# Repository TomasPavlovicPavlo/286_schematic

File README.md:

## Reverse engineering of 286 motherboard
This is the repository vhere I am working on reverse engineering of one 286 motherboard. It is still in progress. I use KiCad. In the PCB editor I insert fotos as background image and draw all tracks. Then I transfer all to schematic and analyse connections.

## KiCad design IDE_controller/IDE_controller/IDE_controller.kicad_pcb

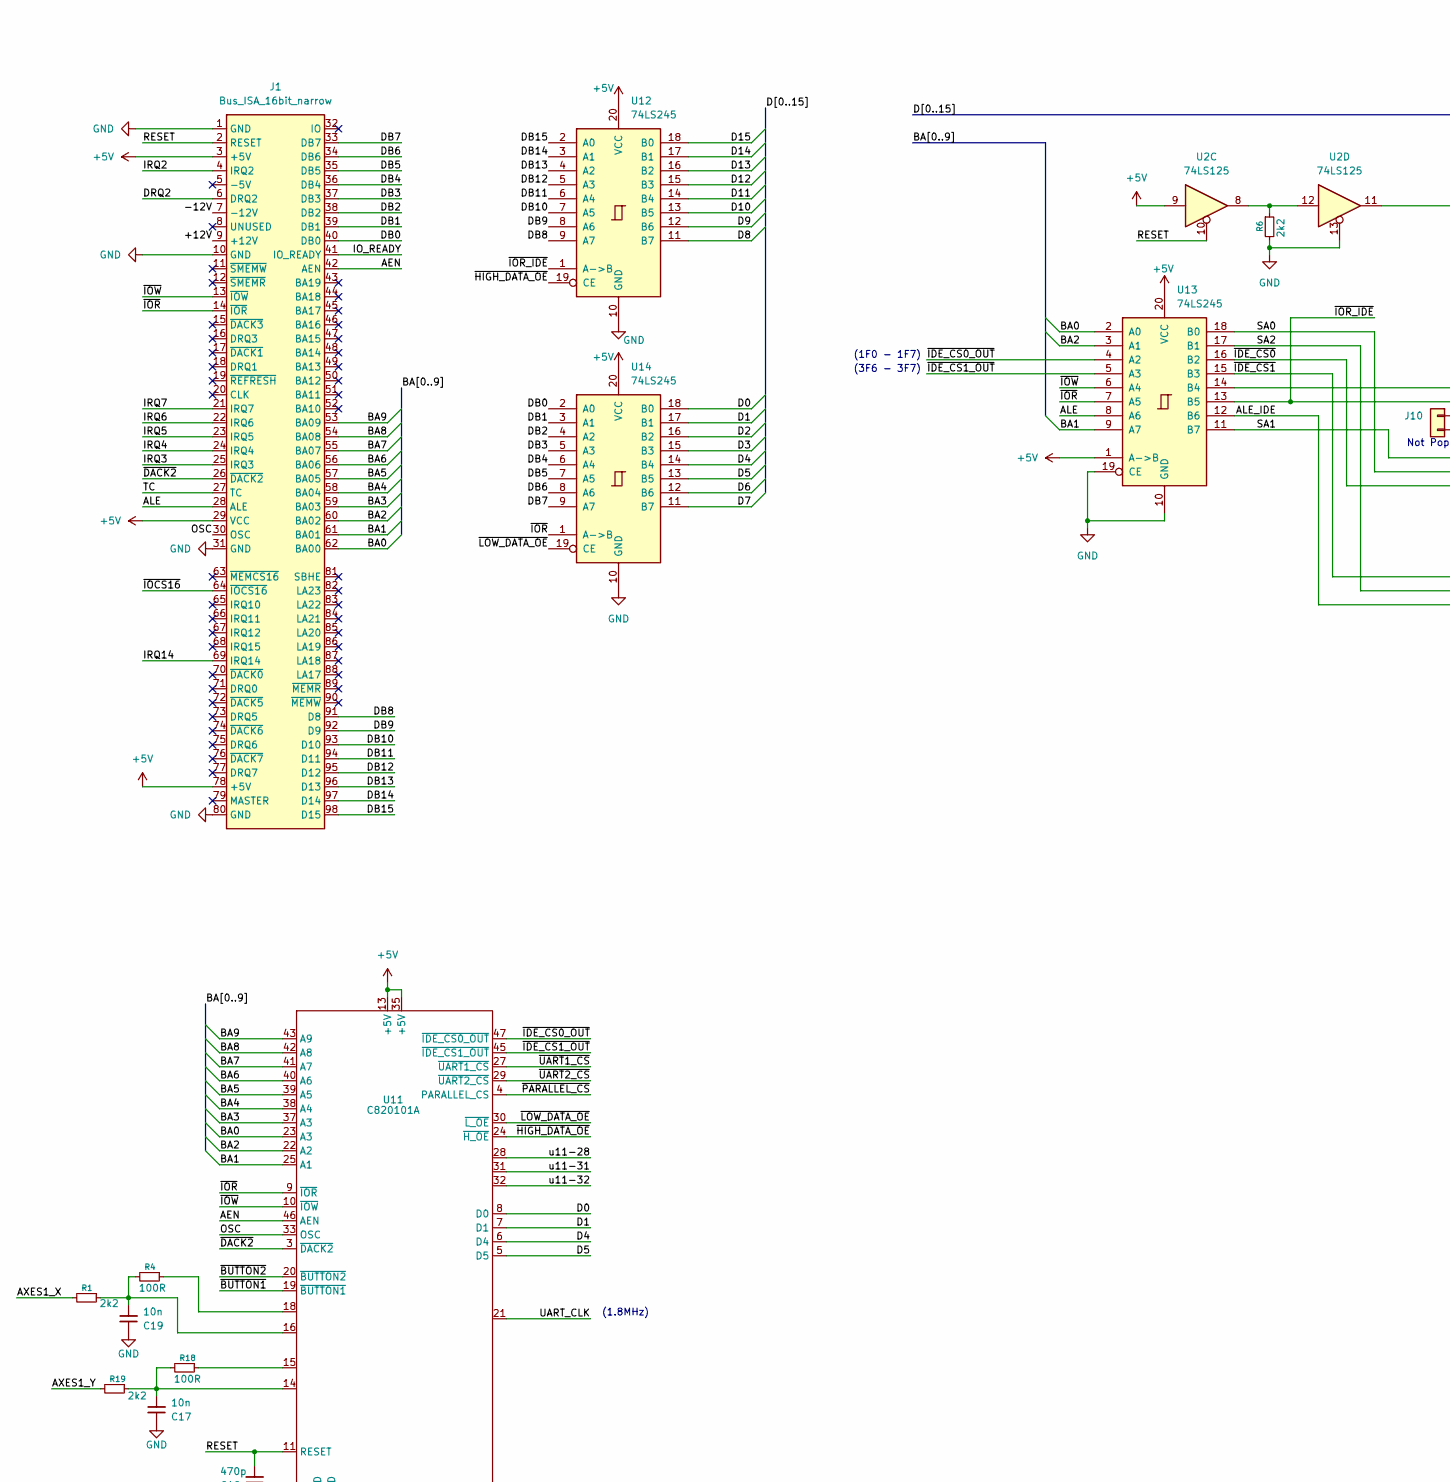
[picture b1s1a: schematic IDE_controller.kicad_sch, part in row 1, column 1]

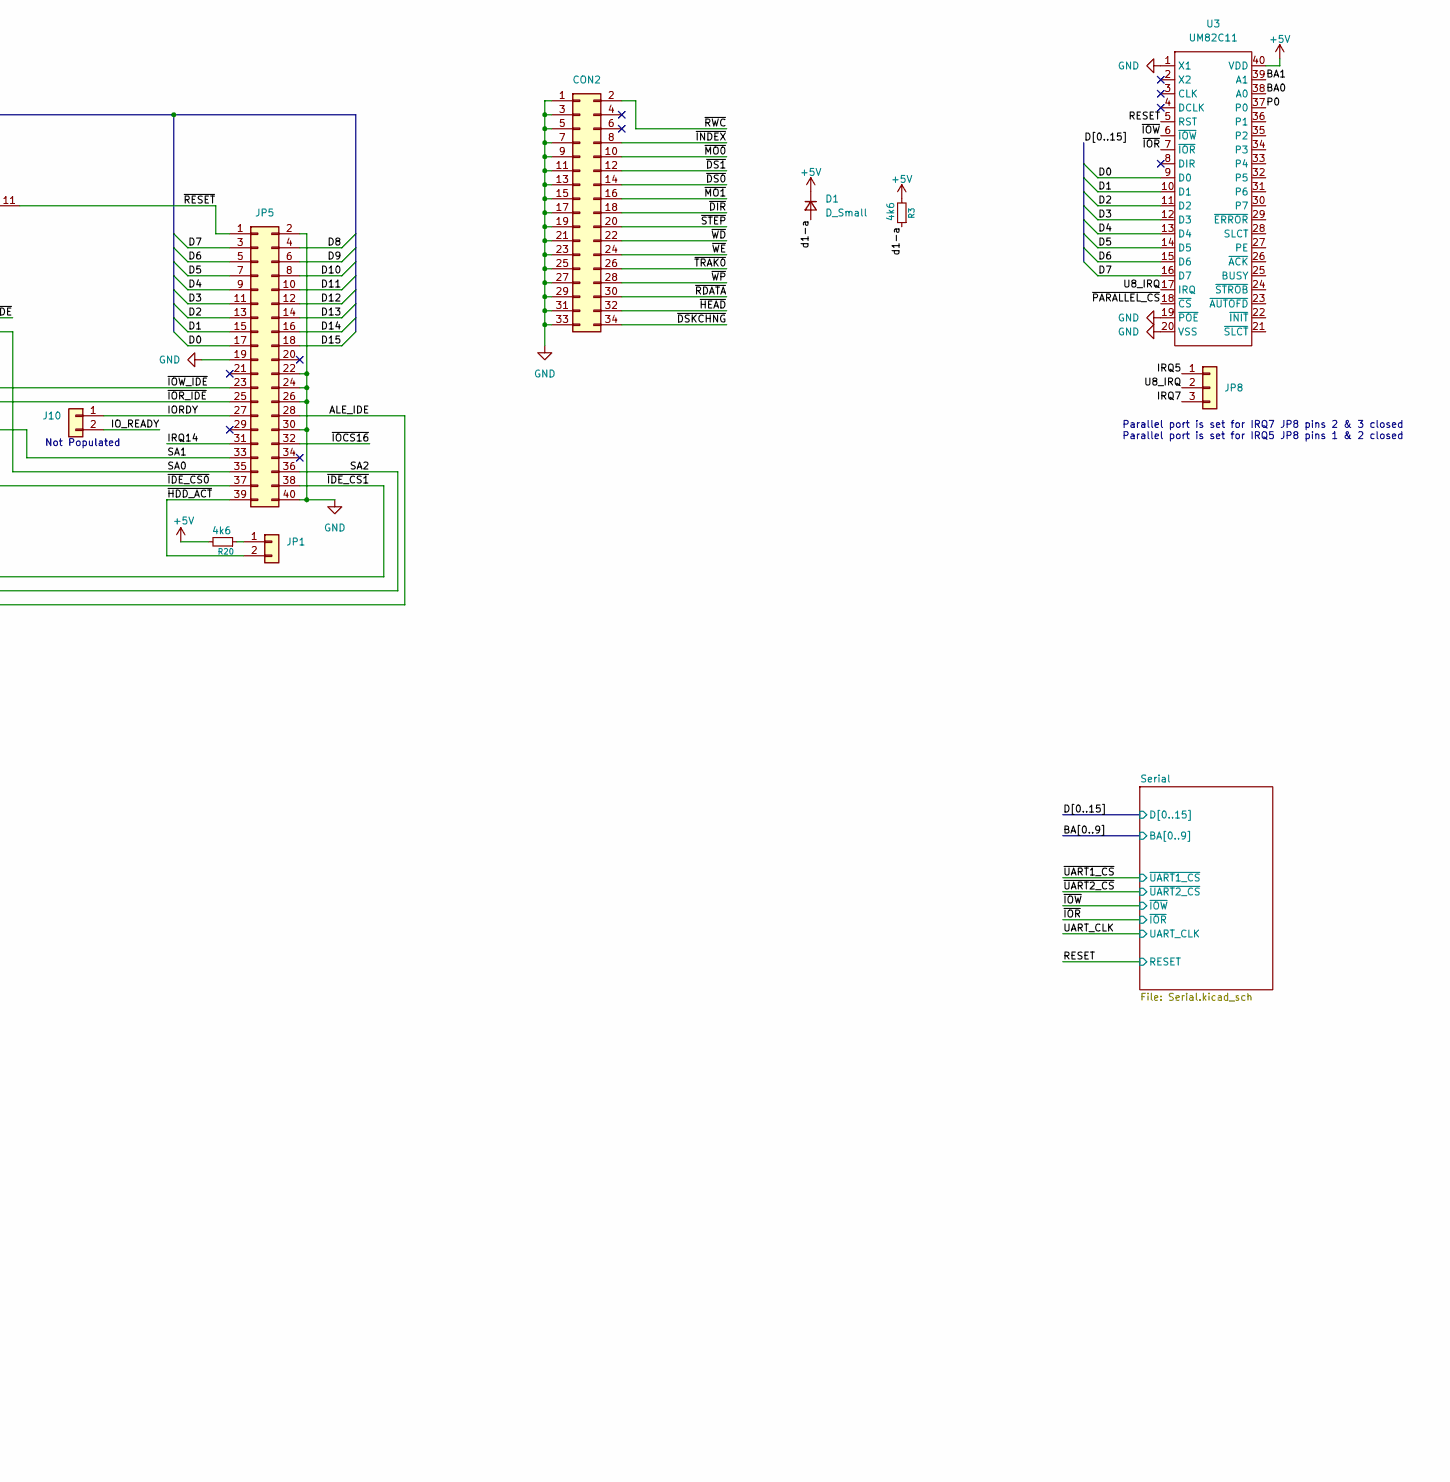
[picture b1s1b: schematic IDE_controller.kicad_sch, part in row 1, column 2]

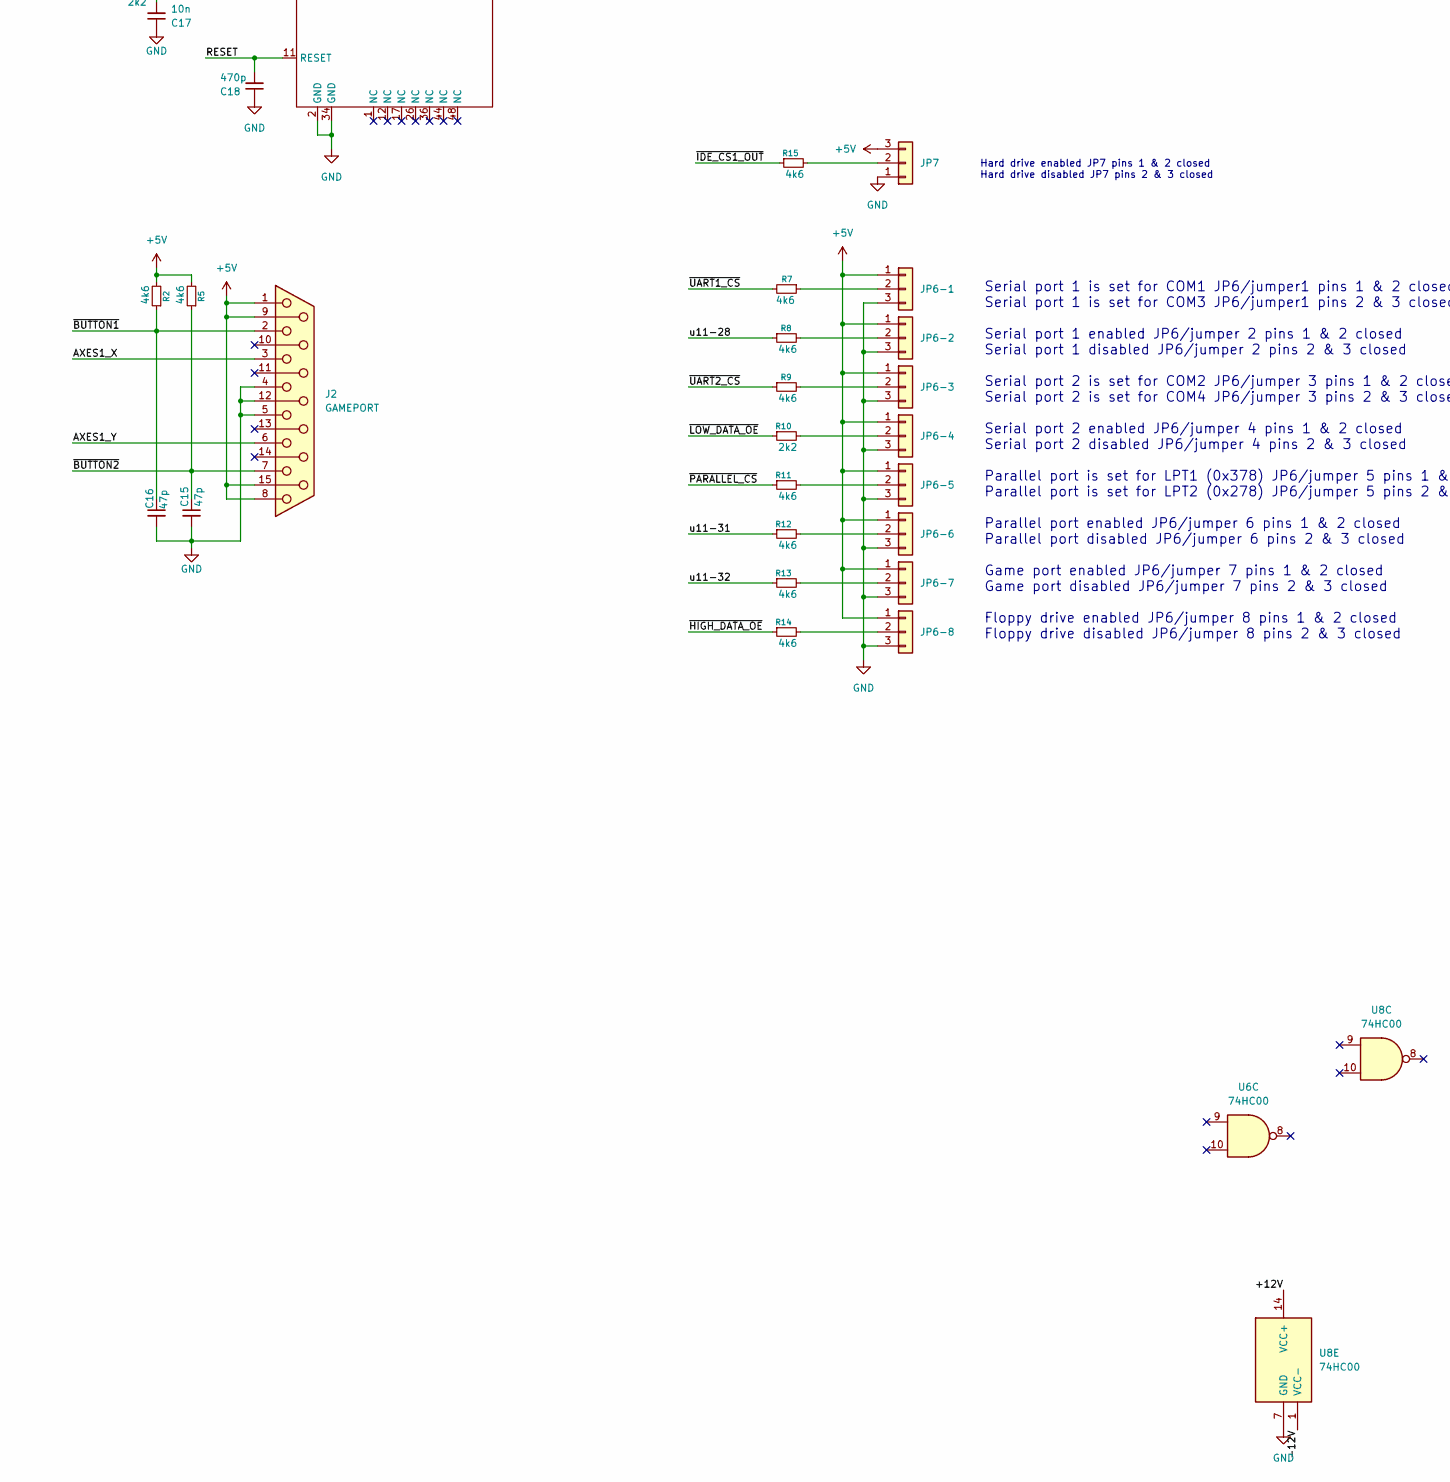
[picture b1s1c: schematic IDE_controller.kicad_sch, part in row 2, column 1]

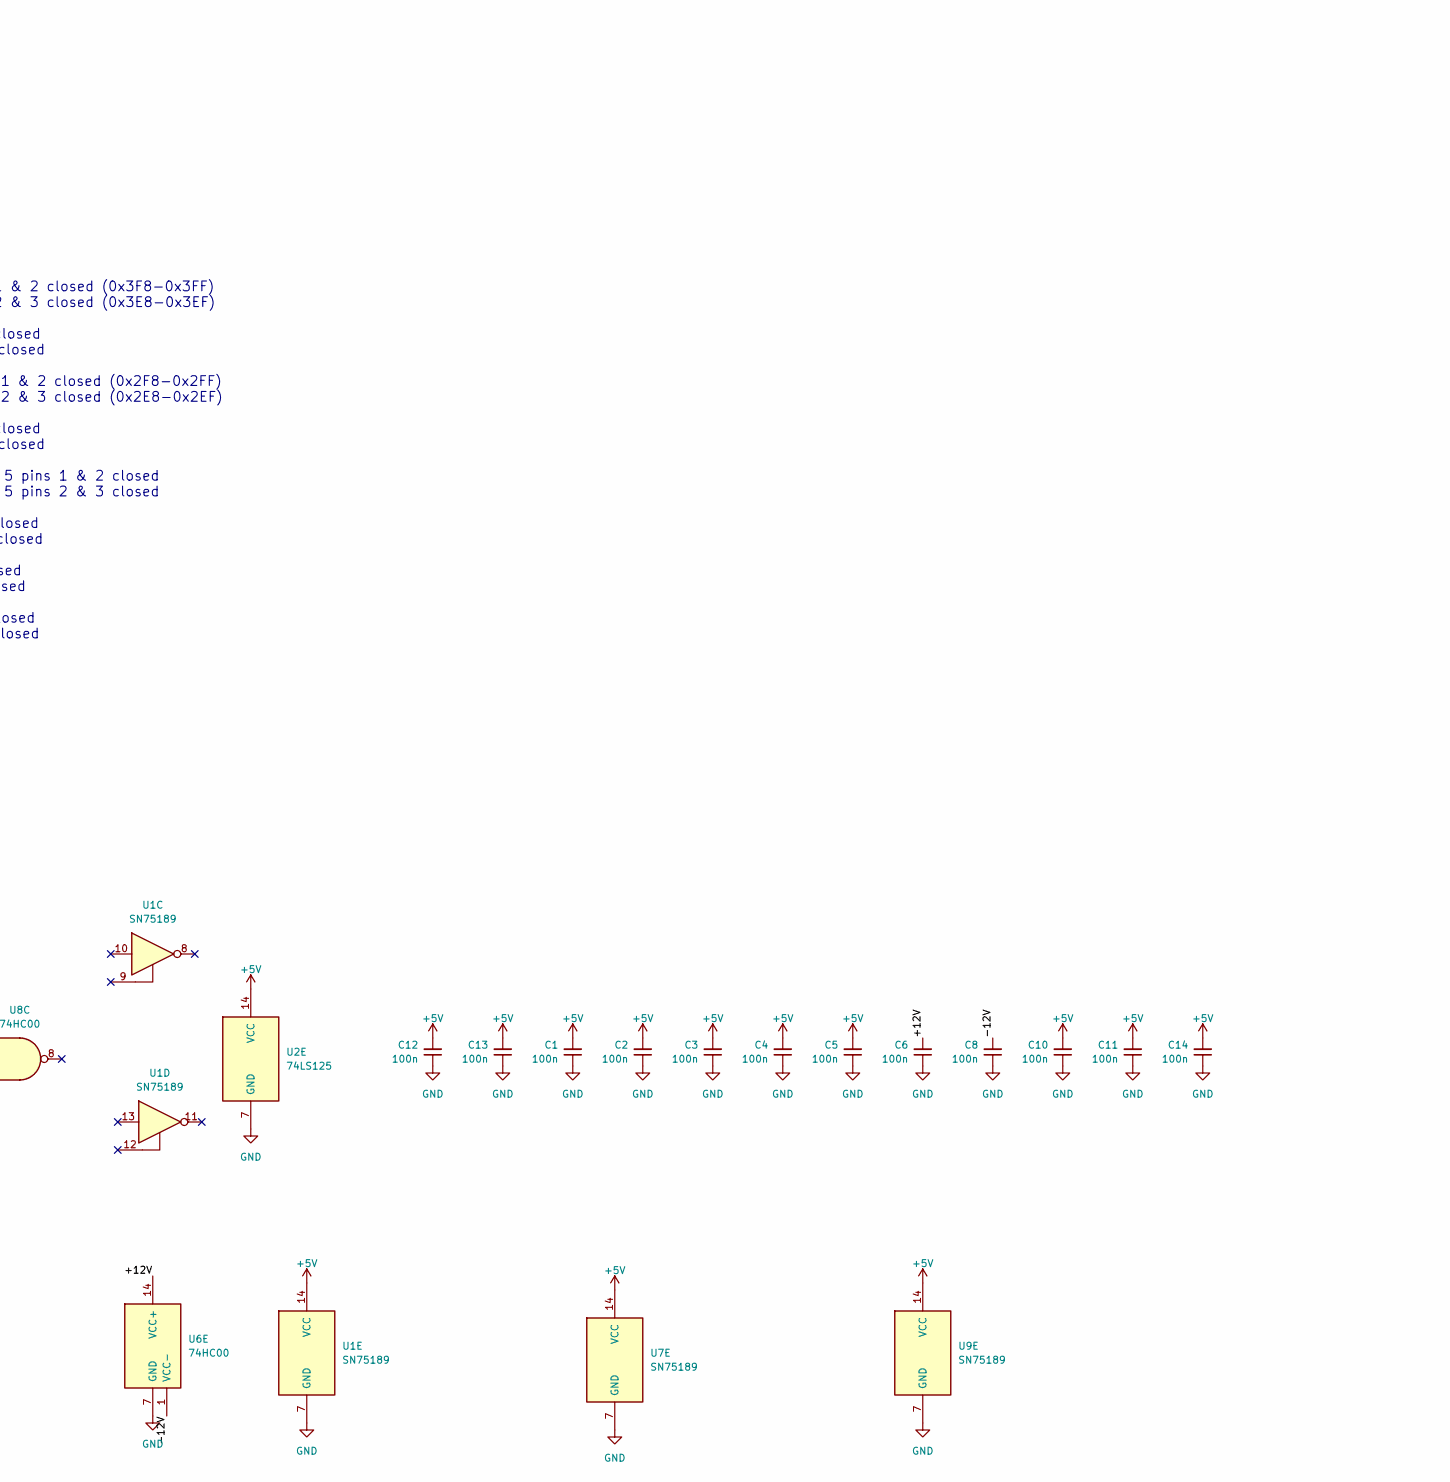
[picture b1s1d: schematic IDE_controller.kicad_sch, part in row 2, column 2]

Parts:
C1, C2, C3, C4, C5, C6, C8, C10, C11, C12, C13, C14: 100n; C_Disc_D4.3mm_W1.9mm_P5.00mm
C15, C16: 47p; C_Disc_D4.3mm_W1.9mm_P5.00mm
C17, C19: 10n; C_Disc_D4.3mm_W1.9mm_P5.00mm
C18: 470p; C_Disc_D4.3mm_W1.9mm_P5.00mm
CON2: Conn_02x17_Odd_Even; PinHeader_2x17_P2.54mm_Vertical
D1: D_Small; D_A-405_P10.16mm_Horizontal
J1: Bus_ISA_16bit_narrow; BUS_AT
J2: GAMEPORT; DSUB-15_Socket_Horizontal_P2.77x2.54mm_EdgePinOffset9.40mm
J10: Conn_01x02; PinHeader_1x02_P2.54mm_Vertical
JP1: Conn_01x02; PinHeader_1x02_P2.54mm_Vertical
JP5: Conn_02x20_Odd_Even; PinHeader_2x20_P2.54mm_Vertical
JP6-1, JP6-2, JP6-3, JP6-4, JP6-5, JP6-6, JP6-7, JP6-8, JP7, JP8: Conn_01x03; PinHeader_1x03_P2.54mm_Vertical
R1, R6, R10, R19: 2k2; R_Axial_DIN0207_L6.3mm_D2.5mm_P10.16mm_Horizontal
R2, R3, R5, R7, R8, R9, R11, R12, R13, R14, R15, R20: 4k6; R_Axial_DIN0207_L6.3mm_D2.5mm_P10.16mm_Horizontal
R4, R18: 100R; R_Axial_DIN0207_L6.3mm_D2.5mm_P10.16mm_Horizontal
U1, U7, U9: SN75189; DIP-14_W7.62mm
U2: 74LS125; DIP-14_W7.62mm
U3: UM82C11; DIP-40_W15.24mm
U6, U8: 74HC00; DIP-14_W7.62mm
U11: C820101A; LQFP-48_10x10mm_P0.7mm
U12, U13, U14: 74LS245; DIP-20_W7.62mm

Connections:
+5V: C1.2, C2.2, C3.2, C4.2, C5.2, C10.2, C11.2, C12.2, C13.2, C14.2, D1.1 (K), J1.3 (+5V), J1.29 (VCC), J1.78 (+5V), J2.1, J2.8, J2.9, J2.15, JP6-1.1, JP6-2.1, JP6-3.1, JP6-4.1, JP6-5.1, JP6-6.1, JP6-7.1, JP6-8.1, JP7.3, R2.2, R3.2, R5.2, R20.2, U1.14 (VCC), U2.9, U2.14 (VCC), U3.40 (VDD), U7.14 (VCC), U9.14 (VCC), U11.13 (+5V), U11.35 (+5V), U12.20 (VCC), U13.1 (A->B), U13.20 (VCC), U14.20 (VCC); also elsewhere on the board
/+12V: C6.2, J1.9 (+12V), U6.14 (VCC+), U8.14 (VCC+)
/-12V: C8.2, J1.7 (-12V), U6.1 (VCC-), U8.1 (VCC-)
/AEN: J1.42 (AEN), U11.46 (AEN)
/ALE: J1.28 (ALE), U13.8 (A6)
/ALE_IDE: JP5.28, U13.12 (B6)
/AXES1_X: J2.3, R1.2
/AXES1_Y: J2.6, R19.2
/BA0: J1.62 (BA00), U3.38 (A0), U11.23 (A3), U13.2 (A0); also elsewhere on the board
/BA1: J1.61 (BA01), U3.39 (A1), U11.25 (A1), U13.9 (A7); also elsewhere on the board
/BA2: J1.60 (BA02), U11.22 (A2), U13.3 (A1); also elsewhere on the board
/BA3: J1.59 (BA03), U11.37 (A3)
/BA4: J1.58 (BA04), U11.38 (A4)
/BA5: J1.57 (BA05), U11.39 (A5)
/BA6: J1.56 (BA06), U11.40 (A6)
/BA7: J1.55 (BA07), U11.41 (A7)
/BA8: J1.54 (BA08), U11.42 (A8)
/BA9: J1.53 (BA09), U11.43 (A9)
/D0: JP5.17, U3.9 (D0), U11.8 (D0), U14.18 (B0); also elsewhere on the board
/D1: JP5.15, U3.10 (D1), U11.7 (D1), U14.17 (B1); also elsewhere on the board
/D2: JP5.13, U3.11 (D2), U14.16 (B2); also elsewhere on the board
/D3: JP5.11, U3.12 (D3), U14.15 (B3); also elsewhere on the board
/D4: JP5.9, U3.13 (D4), U11.6 (D4), U14.14 (B4); also elsewhere on the board
/D5: JP5.7, U3.14 (D5), U11.5 (D5), U14.13 (B5); also elsewhere on the board
/D6: JP5.5, U3.15 (D6), U14.12 (B6); also elsewhere on the board
/D7: JP5.3, U3.16 (D7), U14.11 (B7); also elsewhere on the board
/D8: JP5.4, U12.11 (B7)
/D9: JP5.6, U12.12 (B6)
/D10: JP5.8, U12.13 (B5)
/D11: JP5.10, U12.14 (B4)
/D12: JP5.12, U12.15 (B3)
/D13: JP5.14, U12.16 (B2)
/D14: JP5.16, U12.17 (B1)
/D15: JP5.18, U12.18 (B0)
/DB0: J1.40 (DB0), U14.2 (A0)
/DB1: J1.39 (DB1), U14.3 (A1)
/DB2: J1.38 (DB2), U14.4 (A2)
/DB3: J1.37 (DB3), U14.5 (A3)
/DB4: J1.36 (DB4), U14.6 (A4)
/DB5: J1.35 (DB5), U14.7 (A5)
/DB6: J1.34 (DB6), U14.8 (A6)
/DB7: J1.33 (DB7), U14.9 (A7)
/DB8: J1.91 (D8), U12.9 (A7)
/DB9: J1.92 (D9), U12.8 (A6)
/DB10: J1.93 (D10), U12.7 (A5)
/DB11: J1.94 (D11), U12.6 (A4)
/DB12: J1.95 (D12), U12.5 (A3)
/DB13: J1.96 (D13), U12.4 (A2)
/DB14: J1.97 (D14), U12.3 (A1)
/DB15: J1.98 (D15), U12.2 (A0)
/DRQ2: J1.6 (DRQ2)
/IORDY: J10.1, JP5.27
/IO_READY: J1.41 (IO_READY), J10.2
/IRQ6: J1.22 (IRQ6)
/IRQ7: J1.21 (IRQ7), JP8.3
/IRQ14: J1.69 (IRQ14), JP5.31
/OSC: J1.30 (OSC), U11.33 (OSC)
/P0: U3.37 (P0)
/RESET: C18.2, J1.2 (RESET), U2.10, U3.5 (RST), U11.11 (RESET); also elsewhere on the board
/SA0: JP5.35, U13.18 (B0)
/SA1: JP5.33, U13.11 (B7)
/SA2: JP5.36, U13.17 (B1)
/TC: J1.27 (TC)
/U8_IRQ: JP8.2, U3.17 (IRQ)
/UART_CLK: U11.21; also elsewhere on the board
/d1-a: D1.2 (A), R3.1
/u11-28: R8.1, U11.28
/u11-31: R12.1, U11.31
/u11-32: R13.1, U11.32
/~BUTTON1: C16.1, J2.2, R2.1, U11.19 (~BUTTON1)
/~BUTTON2: C15.1, J2.7, R5.1, U11.20 (~BUTTON2)
/~DACK2: J1.26 (~DACK2), U11.3 (~DACK2)
/~DIR: CON2.18
/~DS0: CON2.14
/~DS1: CON2.12
/~DSKCHNG: CON2.34
/~HDD_ACT: JP1.2, JP5.39
/~HEAD: CON2.32
/~HIGH_DATA_OE: R14.1, U11.24 (~H_OE), U12.19 (CE)
/~IDE_CS0_OUT: U11.47 (~IDE_CS0_OUT), U13.4 (A2)
/~IDE_CS0: JP5.37, U13.16 (B2)
/~IDE_CS1_OUT: R15.1, U11.45 (~IDE_CS1_OUT), U13.5 (A3)
/~IDE_CS1: JP5.38, U13.15 (B3)
/~INDEX: CON2.8
/~IOCS16: J1.64 (~IOCS16), JP5.32
/~IOR_IDE: JP5.25, U12.1 (A->B), U13.13 (B5)
/~IOR: J1.14 (~IOR), U3.7 (~IOR), U11.9 (~IOR), U13.7 (A5), U14.1 (A->B); also elsewhere on the board
/~IOW_IDE: JP5.23, U13.14 (B4)
/~IOW: J1.13 (~IOW), U3.6 (~IOW), U11.10 (~IOW), U13.6 (A4); also elsewhere on the board
/~LOW_DATA_OE: R10.1, U11.30 (~L_OE), U14.19 (CE)
/~MO0: CON2.10
/~MO1: CON2.16
/~PARALLEL_CS: R11.1, U3.18 (~CS), U11.4 (PARALLEL_CS)
/~RDATA: CON2.30
/~RESET: JP5.1, U2.11
/~RWC: CON2.2
/~STEP: CON2.20
/~TRAK0: CON2.26
/~UART1_CS: R7.2, U11.27 (~UART1_CS); also elsewhere on the board
/~UART2_CS: R9.1, U11.29 (~UART2_CS); also elsewhere on the board
/~WD: CON2.22
/~WE: CON2.24
/~WP: CON2.28
GND: C1.1, C2.1, C3.1, C4.1, C5.1, C6.1, C8.1, C10.1, C11.1, C12.1, C13.1, C14.1, C15.2, C16.2, C17.1, C18.1, C19.1, CON2.1, CON2.3, CON2.5, CON2.7, CON2.9, CON2.11, CON2.13, CON2.15, CON2.17, CON2.19, CON2.21, CON2.23, CON2.25, CON2.27, CON2.29, CON2.31, CON2.33, J1.1 (GND), J1.10 (GND), J1.31 (GND), J1.80 (GND), J2.4, J2.5, J2.12, JP5.2, JP5.19, JP5.22, JP5.24, JP5.26, JP5.30, JP5.40, JP6-1.3, JP6-2.3, JP6-3.3, JP6-4.3, JP6-5.3, JP6-6.3, JP6-7.3, JP6-8.3, JP7.1, R6.2, U1.7 (GND), U2.7 (GND), U2.13, U3.1 (X1), U3.19 (~POE), U3.20 (VSS), U6.7 (GND), U7.7 (GND), U8.7 (GND), U9.7 (GND), U11.2 (GND), U11.34 (GND), U12.10 (GND), U13.10 (GND), U13.19 (CE), U14.10 (GND); also elsewhere on the board
IRQ2: J1.4 (IRQ2); also elsewhere on the board
IRQ3: J1.25 (IRQ3); also elsewhere on the board
IRQ4: J1.24 (IRQ4); also elsewhere on the board
IRQ5: J1.23 (IRQ5), JP8.1; also elsewhere on the board
unnamed: C17.2, R18.2, R19.1, U11.14
unnamed: C19.2, R1.1, R4.2, U11.16
unnamed: JP1.1, R20.1
unnamed: JP6-1.2, R7.1
unnamed: JP6-2.2, R8.2
unnamed: JP6-3.2, R9.2
unnamed: JP6-4.2, R10.2
unnamed: JP6-5.2, R11.2
unnamed: JP6-6.2, R12.2
unnamed: JP6-7.2, R13.2
unnamed: JP6-8.2, R14.2
unnamed: JP7.2, R15.2
unnamed: R4.1, U11.18
unnamed: R6.1, U2.8, U2.12
unnamed: R18.1, U11.15

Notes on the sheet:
(3F6 - 3F7)
Not Populated
Serial port 1 is set for COM1 JP6/jumper1 pins 1 & 2 closed (0x3F8-0x3FF) Serial port 1 is set for COM3 JP6/jumper1 pins 2 & 3 closed (0x3E8-0x3EF) Serial port 1 enabled JP6/jumper 2 pins 1 & 2 closed Serial port 1 disabled JP6/jumper 2 pins 2 & 3 closed Serial port 2 is set for COM2 JP6/jumper 3 p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
(1.8MHz)
Parallel port is set for IRQ7 JP8 pins 2 & 3 closed Parallel port is set for IRQ5 JP8 pins 1 & 2 closed
(1F0 - 1F7)
Hard drive enabled JP7 pins 1 & 2 closed Hard drive disabled JP7 pins 2 & 3 closed

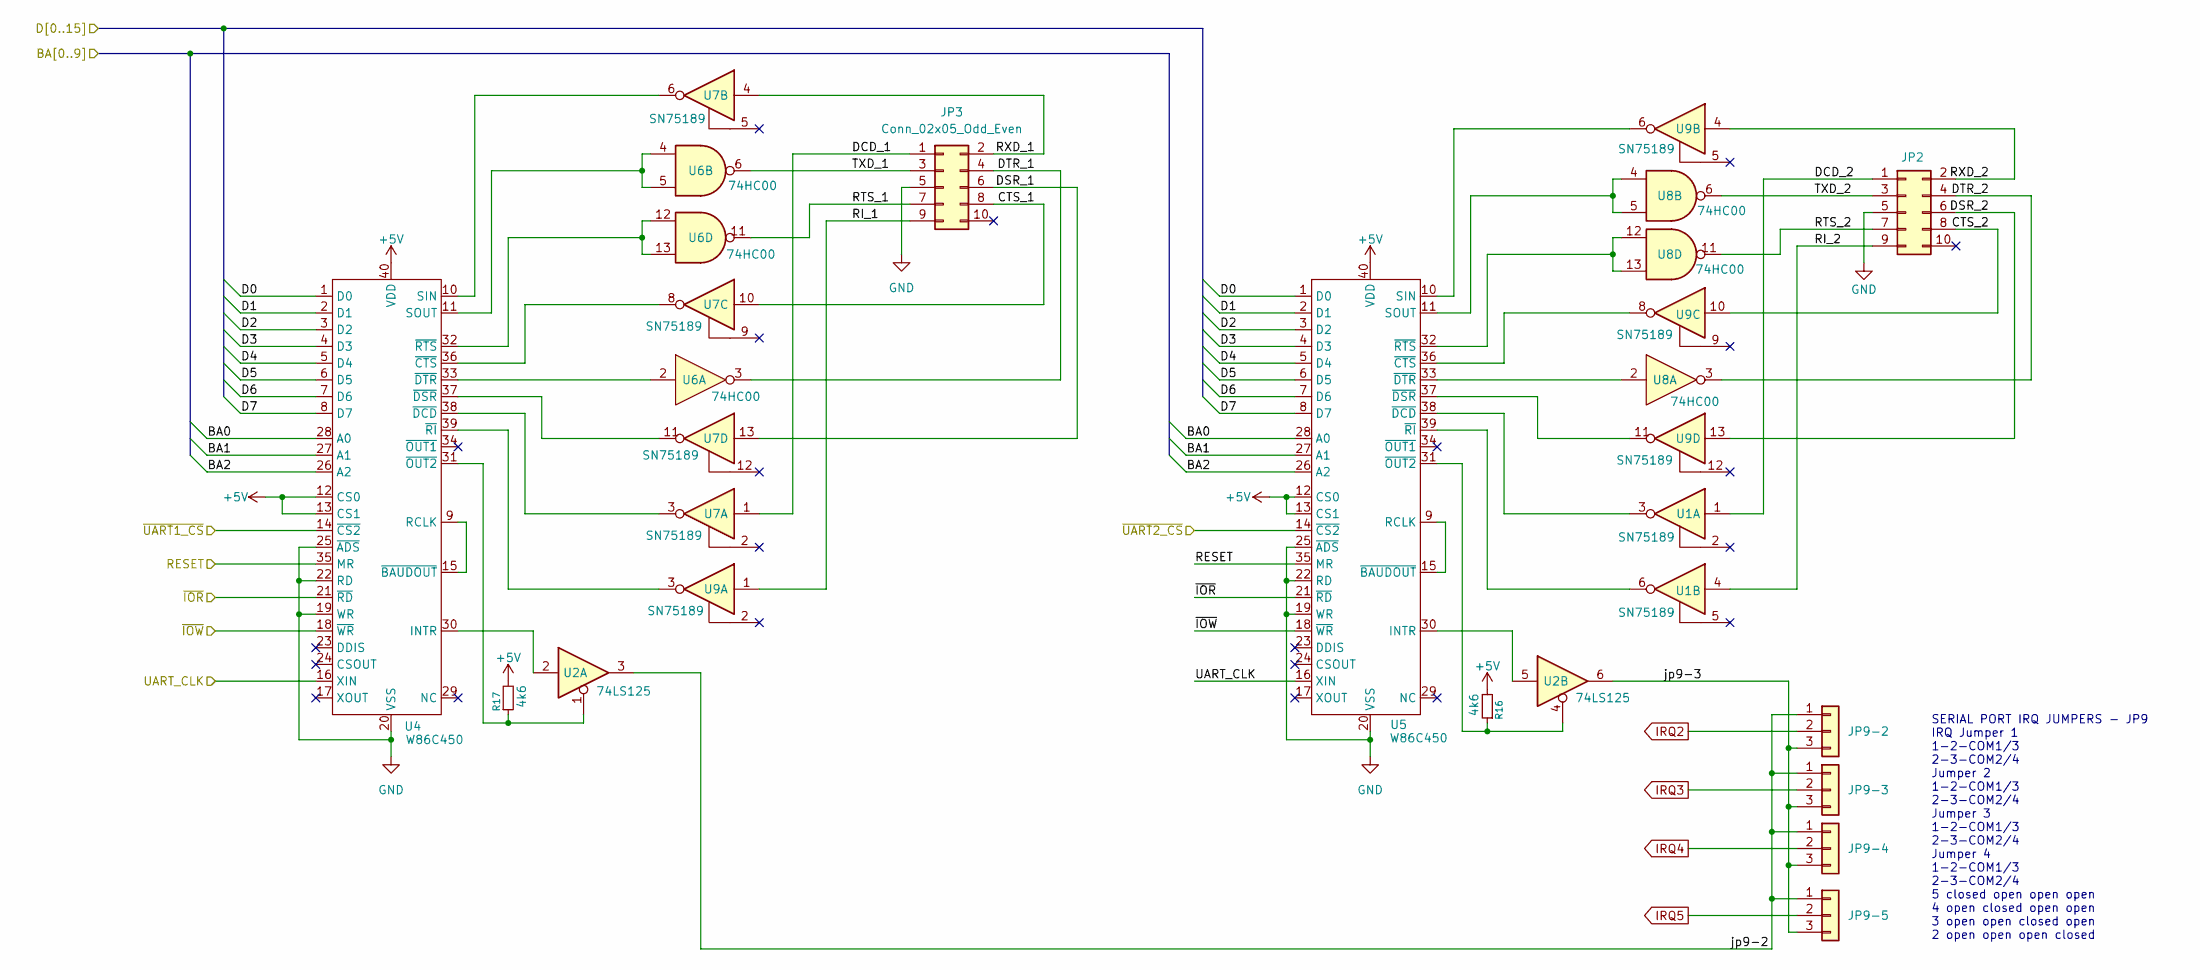
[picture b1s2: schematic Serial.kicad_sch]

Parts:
JP2, JP3: Conn_02x05_Odd_Even; PinHeader_2x05_P2.54mm_Vertical
JP9-2, JP9-3, JP9-4, JP9-5: Conn_01x03; PinHeader_1x03_P2.54mm_Vertical
R16, R17: 4k6; R_Axial_DIN0207_L6.3mm_D2.5mm_P10.16mm_Horizontal
U1, U7, U9: SN75189; DIP-14_W7.62mm
U2: 74LS125; DIP-14_W7.62mm
U4, U5: W86C450; DIP-40_W15.24mm_Socket
U6, U8: 74HC00; DIP-14_W7.62mm

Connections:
+5V: R16.2, R17.2, U4.12 (CS0), U4.13 (CS1), U4.40 (VDD), U5.12 (CS0), U5.13 (CS1), U5.40 (VDD); also elsewhere on the board
/BA0: U4.28 (A0), U5.28 (A0); also elsewhere on the board
/BA1: U4.27 (A1), U5.27 (A1); also elsewhere on the board
/BA2: U4.26 (A2), U5.26 (A2); also elsewhere on the board
/D0: U4.1 (D0), U5.1 (D0); also elsewhere on the board
/D1: U4.2 (D1), U5.2 (D1); also elsewhere on the board
/D2: U4.3 (D2), U5.3 (D2); also elsewhere on the board
/D3: U4.4 (D3), U5.4 (D3); also elsewhere on the board
/D4: U4.5 (D4), U5.5 (D4); also elsewhere on the board
/D5: U4.6 (D5), U5.6 (D5); also elsewhere on the board
/D6: U4.7 (D6), U5.7 (D6); also elsewhere on the board
/D7: U4.8 (D7), U5.8 (D7); also elsewhere on the board
/RESET: U4.35 (MR), U5.35 (MR); also elsewhere on the board
/Serial/CTS_1: JP3.8, U7.10
/Serial/CTS_2: JP2.8, U9.10
/Serial/DCD_1: JP3.1, U7.1
/Serial/DCD_2: JP2.1, U1.1
/Serial/DSR_1: JP3.6, U7.13
/Serial/DSR_2: JP2.6, U9.13
/Serial/DTR_1: JP3.4, U6.3
/Serial/DTR_2: JP2.4, U8.3
/Serial/RI_1: JP3.9, U9.1
/Serial/RI_2: JP2.9, U1.4
/Serial/RTS_1: JP3.7, U6.11
/Serial/RTS_2: JP2.7, U8.11
/Serial/RXD_1: JP3.2, U7.4
/Serial/RXD_2: JP2.2, U9.4
/Serial/TXD_1: JP3.3, U6.6
/Serial/TXD_2: JP2.3, U8.6
/Serial/jp9-2: JP9-2.1, JP9-3.1, JP9-4.1, JP9-5.1, U2.3
/Serial/jp9-3: JP9-2.3, JP9-3.3, JP9-4.3, JP9-5.3, U2.6
/UART_CLK: U4.16 (XIN), U5.16 (XIN); also elsewhere on the board
/~IOR: U4.21 (~RD), U5.21 (~RD); also elsewhere on the board
/~IOW: U4.18 (~WR), U5.18 (~WR); also elsewhere on the board
/~UART1_CS: U4.14 (~CS2); also elsewhere on the board
/~UART2_CS: U5.14 (~CS2); also elsewhere on the board
GND: JP2.5, JP3.5, U4.19 (WR), U4.20 (VSS), U4.22 (RD), U4.25 (~ADS), U5.19 (WR), U5.20 (VSS), U5.22 (RD), U5.25 (~ADS); also elsewhere on the board
IRQ2: JP9-2.2; also elsewhere on the board
IRQ3: JP9-3.2; also elsewhere on the board
IRQ4: JP9-4.2; also elsewhere on the board
IRQ5: JP9-5.2; also elsewhere on the board
unnamed: U2.2, U4.30 (INTR)
unnamed: U4.9 (RCLK), U4.15 (~BAUDOUT)
unnamed: U4.10 (SIN), U7.6
unnamed: U4.11 (SOUT), U6.4, U6.5
unnamed: U4.36 (~CTS), U7.8
unnamed: U4.38 (~DCD), U7.3
unnamed: U4.37 (~DSR), U7.11
unnamed: U4.33 (~DTR), U6.2
unnamed: R17.1, U2.1, U4.31 (~OUT2)
unnamed: U4.39 (~RI), U9.3
unnamed: U4.32 (~RTS), U6.12, U6.13
unnamed: U2.5, U5.30 (INTR)
unnamed: U5.9 (RCLK), U5.15 (~BAUDOUT)
unnamed: U5.10 (SIN), U9.6
unnamed: U5.11 (SOUT), U8.4, U8.5
unnamed: U5.36 (~CTS), U9.8
unnamed: U1.3, U5.38 (~DCD)
unnamed: U5.37 (~DSR), U9.11
unnamed: U5.33 (~DTR), U8.2
unnamed: R16.1, U2.4, U5.31 (~OUT2)
unnamed: U1.6, U5.39 (~RI)
unnamed: U5.32 (~RTS), U8.12, U8.13

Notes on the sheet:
SERIAL PORT IRQ JUMPERS - JP9 IRQ Jumper 1 1-2-COM1/3 2-3-COM2/4 Jumper 2 1-2-COM1/3 2-3-COM2/4 Jumper 3 1-2-COM1/3 2-3-COM2/4 Jumper 4 1-2-COM1/3 2-3-COM2/4 5 closed open open open 4 open closed open open 3 open open closed open 2 open open open closed

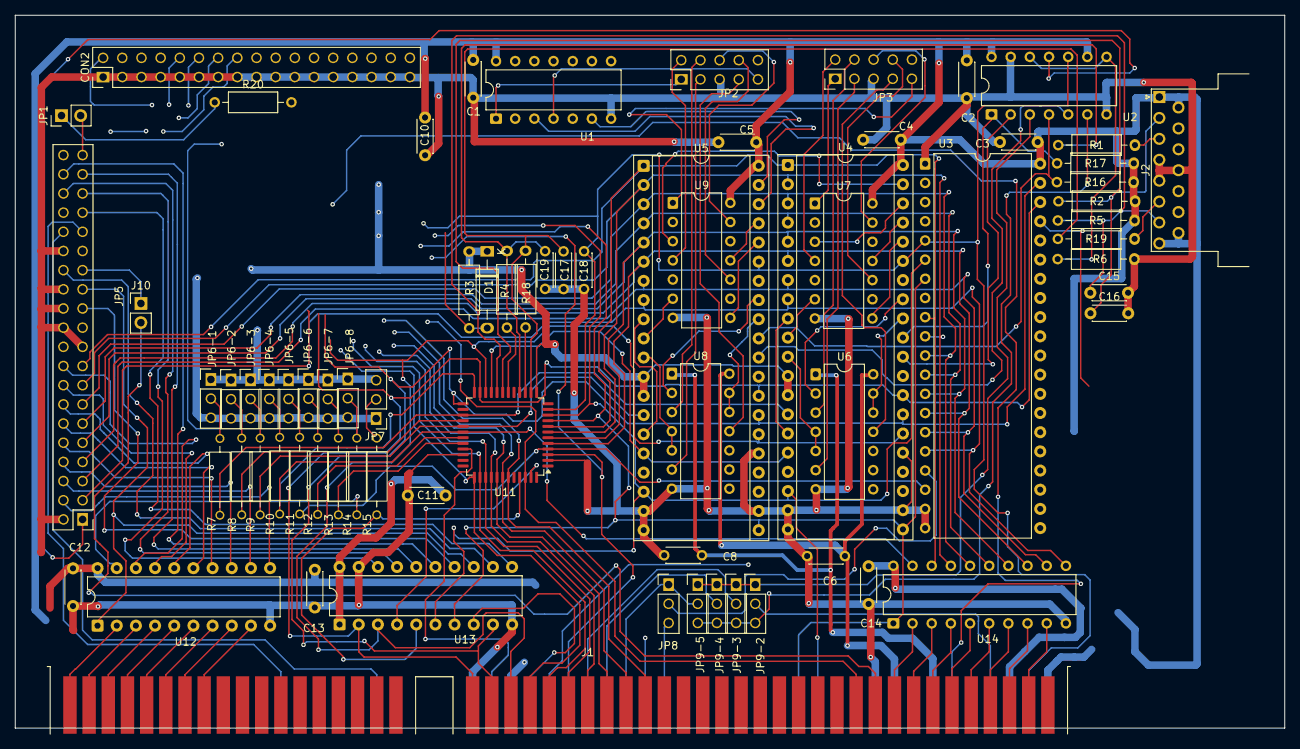
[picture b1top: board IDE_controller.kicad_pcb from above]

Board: 2 copper layers, 168.1 x 94.4 mm, 73 parts (0 on the bottom side), 144 nets.

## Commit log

2025-06-09 DPS update
2025-06-09 PCB update
2025-06-16 PAL decoding
2025-06-20 some pdfs
2025-06-25 schematic update
2025-06-28 schematics update
2025-07-03 Added IDE controller reverse eng
2025-07-03 IDE controller update
2025-07-05 IDE controller update + decoder
2025-07-11 commit from lucky
2025-07-15 ATA reference manual
2025-07-21 286 sch updates
2025-07-28 BIOS captured by logic analyser
2025-07-29 BIOS anasyse
2025-08-03 BIOS 1234 test
